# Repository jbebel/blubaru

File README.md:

# blubaru
Bluetooth interface for my 2000 Subaru Legacy

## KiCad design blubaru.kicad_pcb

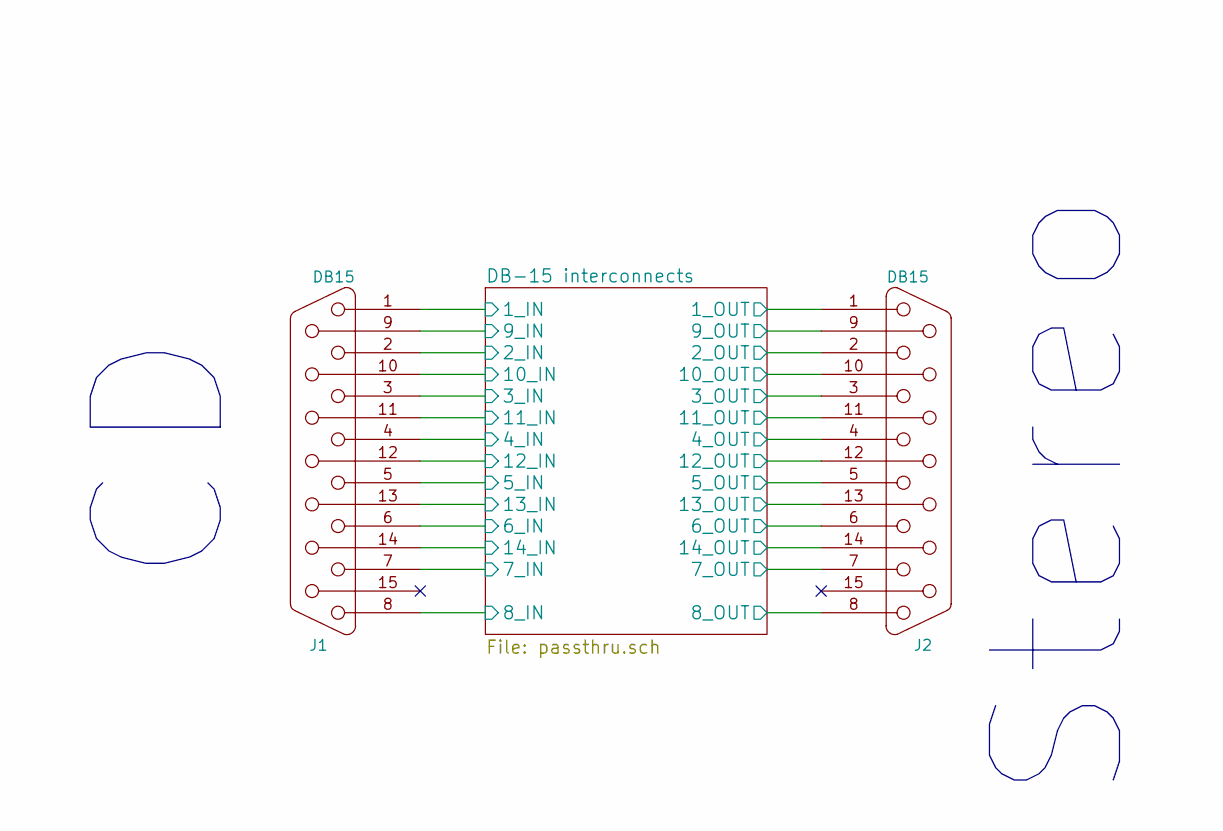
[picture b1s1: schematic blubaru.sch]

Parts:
J1: DB15; DB15FC
J2: DB15; DB15MC

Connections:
+BATT: J1.9, J2.9; also elsewhere on the board
/DB-15 interconnects/1_IN: J1.1, J2.1
/DB-15 interconnects/2_IN: J1.2; also elsewhere on the board
/DB-15 interconnects/2_OUT: J2.2; also elsewhere on the board
/DB-15 interconnects/3_IN: J1.3, J2.3
/DB-15 interconnects/4_IN: J1.4; also elsewhere on the board
/DB-15 interconnects/4_OUT: J2.4; also elsewhere on the board
/DB-15 interconnects/6_IN: J1.6; also elsewhere on the board
/DB-15 interconnects/6_OUT: J2.6; also elsewhere on the board
/DB-15 interconnects/7_IN: J1.7, J2.7
/DB-15 interconnects/8_IN: J1.8, J2.8
/DB-15 interconnects/10_IN: J1.10, J2.10
/DB-15 interconnects/11_IN: J1.11 (P111), J2.11 (P111)
/DB-15 interconnects/12_IN: J1.12, J2.12
/DB-15 interconnects/13_IN: J1.13, J2.13
GND: J1.14, J2.14; also elsewhere on the board
GNDA: J1.5, J2.5; also elsewhere on the board

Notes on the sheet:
Stereo

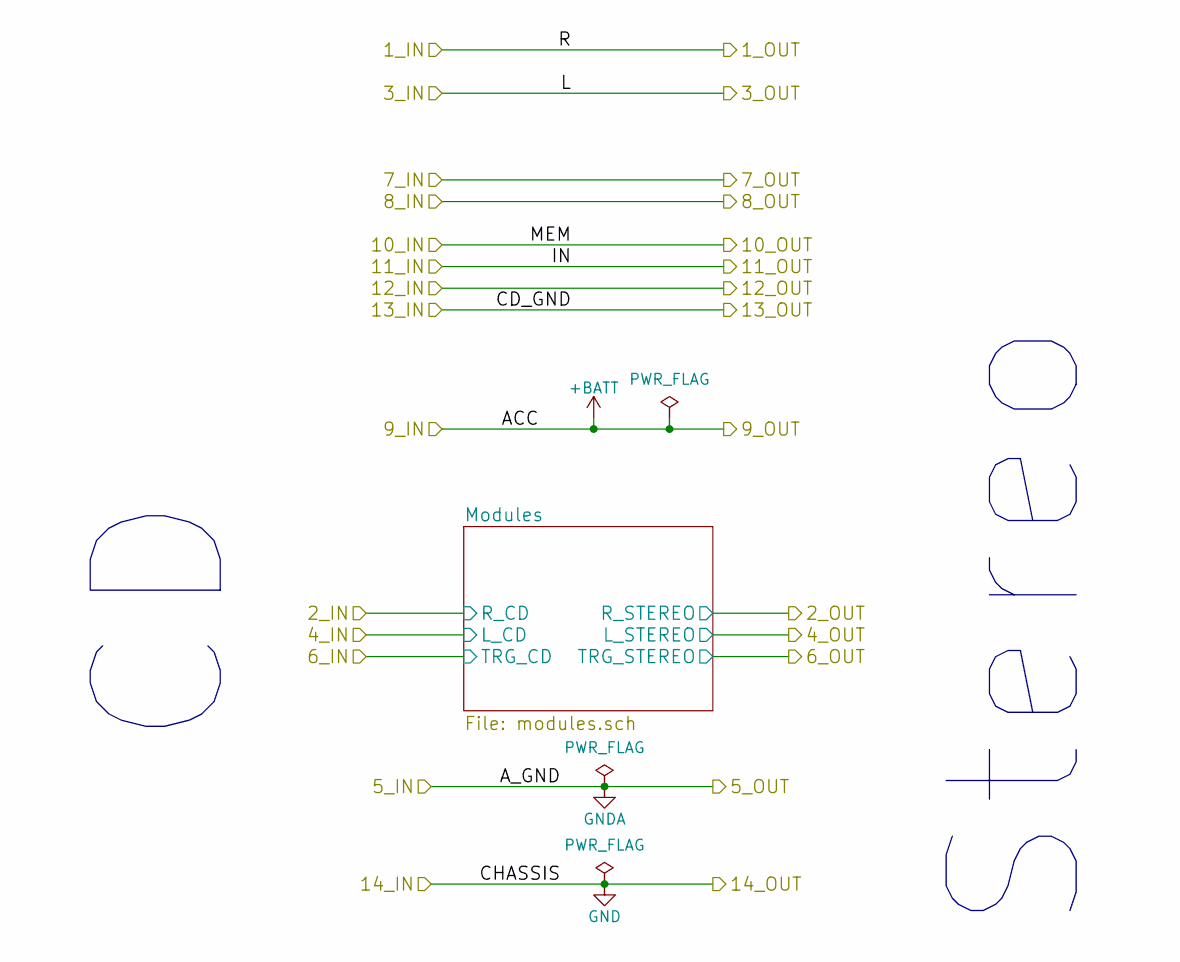
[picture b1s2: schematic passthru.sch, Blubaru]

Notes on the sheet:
Stereo

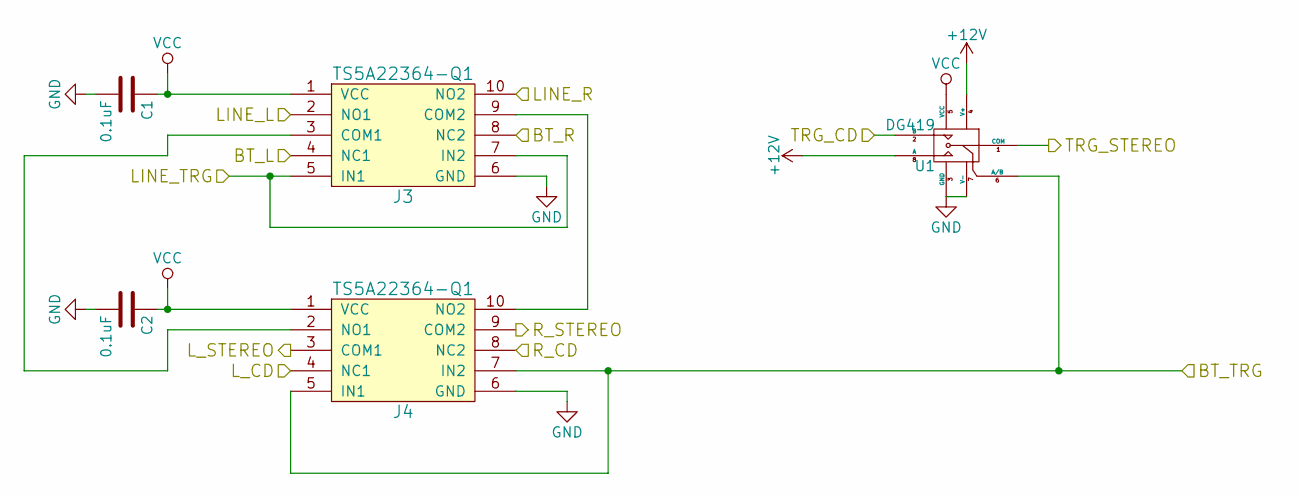
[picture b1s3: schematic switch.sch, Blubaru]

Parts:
C1, C2: 0.1uF; C_Disc_D4.0mm_W2.6mm_P2.50mm
J3, J4: TS5A22364-Q1
U1: DG419; DIP-8_W7.62mm

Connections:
+12V: U1.4 (V+), U1.8 (A); also elsewhere on the board
/DB-15 interconnects/2_IN: J4.8 (NC2); also elsewhere on the board
/DB-15 interconnects/2_OUT: J4.9 (COM2); also elsewhere on the board
/DB-15 interconnects/4_IN: J4.4 (NC1); also elsewhere on the board
/DB-15 interconnects/4_OUT: J4.3 (COM1); also elsewhere on the board
/DB-15 interconnects/6_IN: U1.2 (B); also elsewhere on the board
/DB-15 interconnects/6_OUT: U1.1 (COM); also elsewhere on the board
/DB-15 interconnects/Modules/Audio switch/BT_L: J3.4 (NC1); also elsewhere on the board
/DB-15 interconnects/Modules/Audio switch/BT_R: J3.8 (NC2); also elsewhere on the board
/DB-15 interconnects/Modules/Audio switch/BT_TRG: J4.5 (IN1), J4.7 (IN2), U1.6 (A/B); also elsewhere on the board
/DB-15 interconnects/Modules/Audio switch/LINE_L: J3.2 (NO1); also elsewhere on the board
/DB-15 interconnects/Modules/Audio switch/LINE_R: J3.10 (NO2); also elsewhere on the board
/DB-15 interconnects/Modules/Audio switch/LINE_TRG: J3.5 (IN1), J3.7 (IN2); also elsewhere on the board
GND: C1.2, C2.2, J3.6 (GND), J4.6 (GND), U1.3 (GND), U1.7 (V-); also elsewhere on the board
unnamed: J3.3 (COM1), J4.2 (NO1)
unnamed: J3.9 (COM2), J4.10 (NO2)
VCC: C1.1, C2.1, J3.1 (VCC), J4.1 (VCC), U1.5 (VCC); also elsewhere on the board

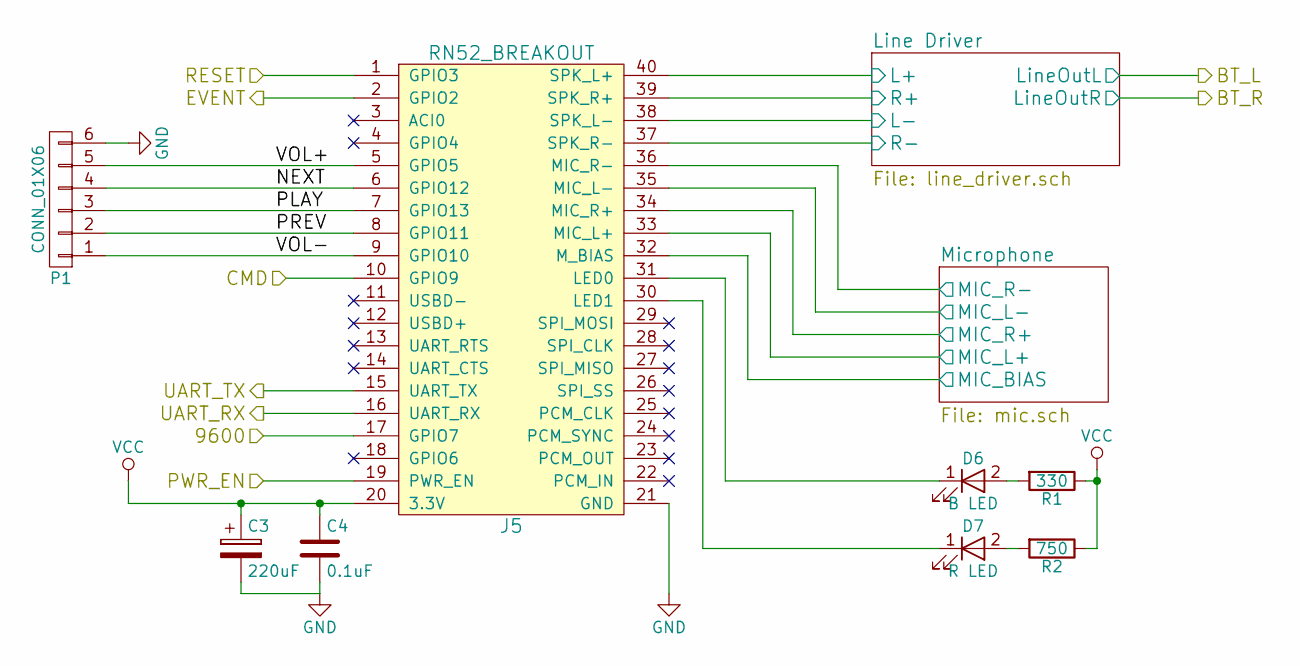
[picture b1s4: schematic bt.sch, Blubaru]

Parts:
C3: 220uF; CP_Radial_D6.3mm_P2.50mm
C4: 0.1uF; C_Disc_D4.0mm_W2.6mm_P2.50mm
D6: B LED; LED_D3.0mm_Horizontal_O1.27mm_Z6.0mm
D7: R LED; LED_D3.0mm_Horizontal_O1.27mm_Z6.0mm
J5: RN52_BREAKOUT; RN52_Breakout
P1: CONN_01X06; Pin_Header_Straight_1x06_Pitch2.54mm
R1: 330; R_Axial_DIN0204_L3.6mm_D1.6mm_P5.08mm_Horizontal
R2: 750; R_Axial_DIN0204_L3.6mm_D1.6mm_P5.08mm_Horizontal

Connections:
/DB-15 interconnects/Modules/Bluetooth Module/9600: J5.17 (GPIO7); also elsewhere on the board
/DB-15 interconnects/Modules/Bluetooth Module/CMD: J5.10 (GPIO9); also elsewhere on the board
/DB-15 interconnects/Modules/Bluetooth Module/EVENT: J5.2 (GPIO2); also elsewhere on the board
/DB-15 interconnects/Modules/Bluetooth Module/Line Driver/L+: J5.40 (SPK_L+); also elsewhere on the board
/DB-15 interconnects/Modules/Bluetooth Module/Line Driver/L-: J5.38 (SPK_L-); also elsewhere on the board
/DB-15 interconnects/Modules/Bluetooth Module/Line Driver/R+: J5.39 (SPK_R+); also elsewhere on the board
/DB-15 interconnects/Modules/Bluetooth Module/Line Driver/R-: J5.37 (SPK_R-); also elsewhere on the board
/DB-15 interconnects/Modules/Bluetooth Module/Microphone/MIC_BIAS: J5.32 (M_BIAS); also elsewhere on the board
/DB-15 interconnects/Modules/Bluetooth Module/Microphone/MIC_L+: J5.33 (MIC_L+); also elsewhere on the board
/DB-15 interconnects/Modules/Bluetooth Module/Microphone/MIC_L-: J5.35 (MIC_L-); also elsewhere on the board
/DB-15 interconnects/Modules/Bluetooth Module/Microphone/MIC_R+: J5.34 (MIC_R+); also elsewhere on the board
/DB-15 interconnects/Modules/Bluetooth Module/Microphone/MIC_R-: J5.36 (MIC_R-); also elsewhere on the board
/DB-15 interconnects/Modules/Bluetooth Module/NEXT: J5.6 (GPIO12), P1.4
/DB-15 interconnects/Modules/Bluetooth Module/PLAY: J5.7 (GPIO13), P1.3
/DB-15 interconnects/Modules/Bluetooth Module/PREV: J5.8 (GPIO11), P1.2
/DB-15 interconnects/Modules/Bluetooth Module/PWR_EN: J5.19 (PWR_EN); also elsewhere on the board
/DB-15 interconnects/Modules/Bluetooth Module/UART_RX: J5.16 (UART_RX); also elsewhere on the board
/DB-15 interconnects/Modules/Bluetooth Module/UART_TX: J5.15 (UART_TX); also elsewhere on the board
/DB-15 interconnects/Modules/Bluetooth Module/VOL+: J5.5 (GPIO5), P1.5
/DB-15 interconnects/Modules/Bluetooth Module/VOL-: J5.9 (GPIO10), P1.1
/DB-15 interconnects/Modules/Microcontroller/BT_RESET: J5.1 (GPIO3); also elsewhere on the board
GND: C3.2, C4.2, J5.21 (GND), P1.6; also elsewhere on the board
unnamed: D6.1 (K), J5.31 (LED0)
unnamed: D6.2 (A), R1.2
unnamed: D7.1 (K), J5.30 (LED1)
unnamed: D7.2 (A), R2.2
VCC: C3.1, C4.1, J5.20 (3.3V), R1.1, R2.1; also elsewhere on the board

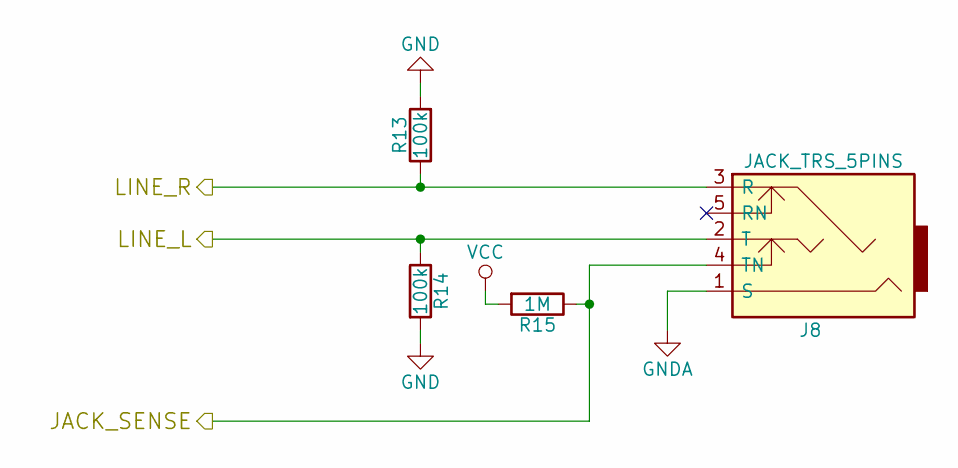
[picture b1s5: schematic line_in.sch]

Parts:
J8: JACK_TRS_5PINS; sj1-353xng
R13, R14: 100k; R_Axial_DIN0204_L3.6mm_D1.6mm_P5.08mm_Horizontal
R15: 1M; R_Axial_DIN0204_L3.6mm_D1.6mm_P5.08mm_Horizontal

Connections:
/DB-15 interconnects/Modules/Audio switch/LINE_L: J8.2 (T), R14.1; also elsewhere on the board
/DB-15 interconnects/Modules/Audio switch/LINE_R: J8.3 (R), R13.1; also elsewhere on the board
/DB-15 interconnects/Modules/Line In/JACK_SENSE: J8.4 (TN), R15.1; also elsewhere on the board
GND: R13.2, R14.2; also elsewhere on the board
GNDA: J8.1 (S); also elsewhere on the board
VCC: R15.2; also elsewhere on the board

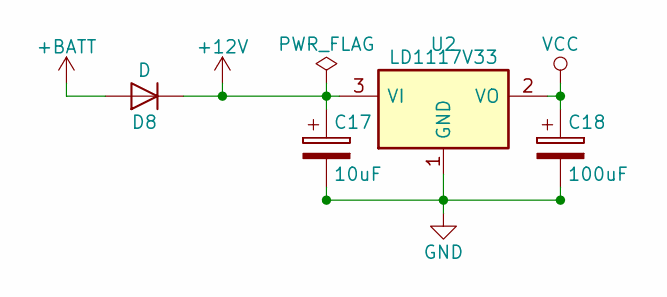
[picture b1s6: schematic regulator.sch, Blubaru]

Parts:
C17: 10uF; CP_Radial_D4.0mm_P1.50mm
C18: 100uF; CP_Radial_D6.3mm_P2.50mm
D8: D; D_DO-41_SOD81_P7.62mm_Horizontal
U2: LD1117V33; TO-220_Vertical

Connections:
+12V: C17.1, D8.1 (K), U2.3 (VI); also elsewhere on the board
+BATT: D8.2 (A); also elsewhere on the board
GND: C17.2, C18.2, U2.1 (GND); also elsewhere on the board
VCC: C18.1, U2.2 (VO); also elsewhere on the board

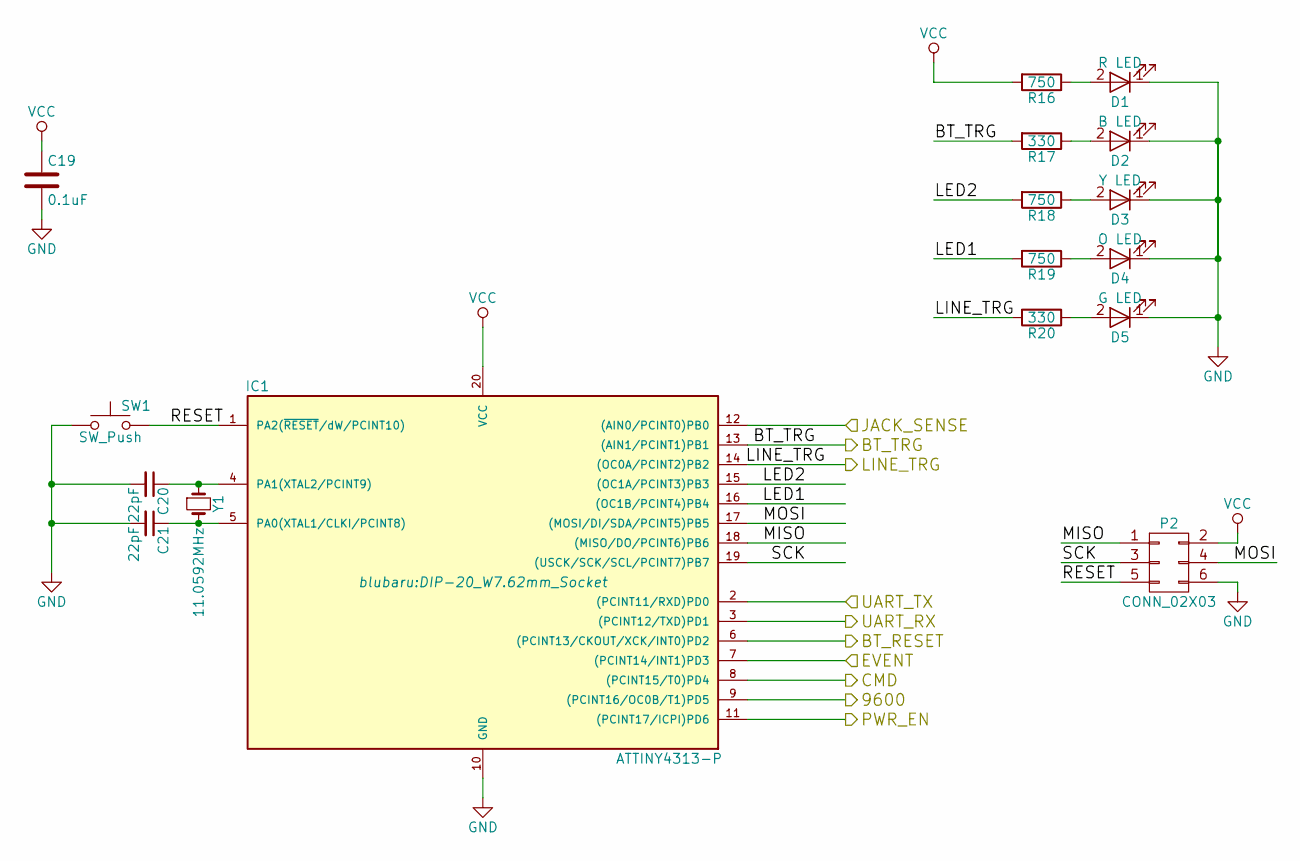
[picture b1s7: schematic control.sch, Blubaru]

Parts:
C19: 0.1uF; C_Disc_D4.0mm_W2.6mm_P2.50mm
C20, C21: 22pF; C_Disc_D4.0mm_W2.6mm_P2.50mm
D1: R LED; LED_D3.0mm_Horizontal_O1.27mm_Z6.0mm
D2: B LED; LED_D3.0mm_Horizontal_O1.27mm_Z6.0mm
D3: Y LED; LED_D3.0mm_Horizontal_O1.27mm_Z6.0mm
D4: O LED; LED_D3.0mm_Horizontal_O1.27mm_Z6.0mm
D5: G LED; LED_D3.0mm_Horizontal_O1.27mm_Z6.0mm
IC1: ATTINY4313-P; DIP-20_W7.62mm_Socket
P2: CONN_02X03; Pin_Header_Straight_2x03_Pitch2.54mm
R16, R18, R19: 750; R_Axial_DIN0204_L3.6mm_D1.6mm_P5.08mm_Horizontal
R17, R20: 330; R_Axial_DIN0204_L3.6mm_D1.6mm_P5.08mm_Horizontal
SW1: SW_Push; SW_Tactile_SPST_Angled_PTS645Vx58-2LFS
Y1: 11.0592MHz; Crystal_HC49-4H_Vertical

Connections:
/DB-15 interconnects/Modules/Audio switch/BT_TRG: IC1.13 ((AIN1/PCINT1)PB1), R17.2; also elsewhere on the board
/DB-15 interconnects/Modules/Audio switch/LINE_TRG: IC1.14 ((OC0A/PCINT2)PB2), R20.2; also elsewhere on the board
/DB-15 interconnects/Modules/Bluetooth Module/9600: IC1.9 ((PCINT16/OC0B/T1)PD5); also elsewhere on the board
/DB-15 interconnects/Modules/Bluetooth Module/CMD: IC1.8 ((PCINT15/T0)PD4); also elsewhere on the board
/DB-15 interconnects/Modules/Bluetooth Module/EVENT: IC1.7 ((PCINT14/INT1)PD3); also elsewhere on the board
/DB-15 interconnects/Modules/Bluetooth Module/PWR_EN: IC1.11 ((PCINT17/ICPI)PD6); also elsewhere on the board
/DB-15 interconnects/Modules/Bluetooth Module/UART_RX: IC1.3 ((PCINT12/TXD)PD1); also elsewhere on the board
/DB-15 interconnects/Modules/Bluetooth Module/UART_TX: IC1.2 ((PCINT11/RXD)PD0); also elsewhere on the board
/DB-15 interconnects/Modules/Line In/JACK_SENSE: IC1.12 ((AIN0/PCINT0)PB0); also elsewhere on the board
/DB-15 interconnects/Modules/Microcontroller/BT_RESET: IC1.6 ((PCINT13/CKOUT/XCK/INT0)PD2); also elsewhere on the board
/DB-15 interconnects/Modules/Microcontroller/LED1: IC1.16 ((OC1B/PCINT4)PB4), R19.2
/DB-15 interconnects/Modules/Microcontroller/LED2: IC1.15 ((OC1A/PCINT3)PB3), R18.2
/DB-15 interconnects/Modules/Microcontroller/MISO: IC1.18 ((MISO/DO/PCINT6)PB6), P2.1
/DB-15 interconnects/Modules/Microcontroller/MOSI: IC1.17 ((MOSI/DI/SDA/PCINT5)PB5), P2.4
/DB-15 interconnects/Modules/Microcontroller/RESET: IC1.1 (PA2(~RESET~/dW/PCINT10)), P2.5, SW1.2
/DB-15 interconnects/Modules/Microcontroller/SCK: IC1.19 ((USCK/SCK/SCL/PCINT7)PB7), P2.3
GND: C19.2, C20.2, C21.2, D1.1 (K), D2.1 (K), D3.1 (K), D4.1 (K), D5.1 (K), IC1.10 (GND), P2.6, SW1.1; also elsewhere on the board
unnamed: C20.1, IC1.4 (PA1(XTAL2/PCINT9)), Y1.1
unnamed: C21.1, IC1.5 (PA0(XTAL1/CLKI/PCINT8)), Y1.2
unnamed: D1.2 (A), R16.1
unnamed: D2.2 (A), R17.1
unnamed: D3.2 (A), R18.1
unnamed: D4.2 (A), R19.1
unnamed: D5.2 (A), R20.1
VCC: C19.1, IC1.20 (VCC), P2.2, R16.2; also elsewhere on the board

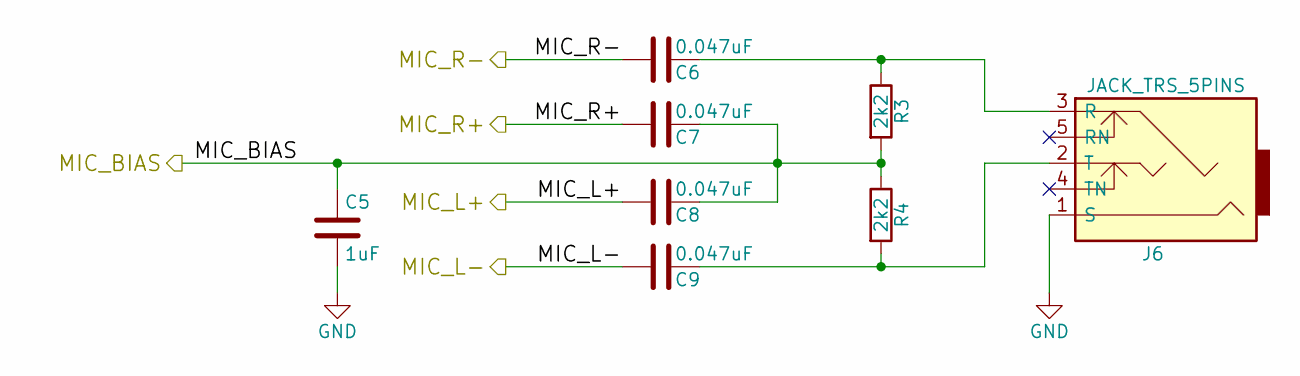
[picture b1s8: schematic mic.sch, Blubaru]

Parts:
C5: 1uF; C_Disc_D5.0mm_W3.2mm_P2.50mm
C6, C7, C8, C9: 0.047uF; C_Disc_D4.0mm_W2.6mm_P2.50mm
J6: JACK_TRS_5PINS; sj1-353xng
R3, R4: 2k2; R_Axial_DIN0204_L3.6mm_D1.6mm_P5.08mm_Horizontal

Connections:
/DB-15 interconnects/Modules/Bluetooth Module/Microphone/MIC_BIAS: C5.1, C7.1, C8.1, R3.2, R4.1; also elsewhere on the board
/DB-15 interconnects/Modules/Bluetooth Module/Microphone/MIC_L+: C8.2; also elsewhere on the board
/DB-15 interconnects/Modules/Bluetooth Module/Microphone/MIC_L-: C9.2; also elsewhere on the board
/DB-15 interconnects/Modules/Bluetooth Module/Microphone/MIC_R+: C7.2; also elsewhere on the board
/DB-15 interconnects/Modules/Bluetooth Module/Microphone/MIC_R-: C6.2; also elsewhere on the board
GND: C5.2, J6.1 (S); also elsewhere on the board
unnamed: C6.1, J6.3 (R), R3.1
unnamed: C9.1, J6.2 (T), R4.2

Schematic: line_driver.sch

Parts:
C10, C12, C14, C16: 1uF; CP_Radial_D4.0mm_P1.50mm
C11, C13, C15: 1uF; C_Disc_D5.0mm_W3.2mm_P2.50mm
J7: DRV632
R5, R8, R9, R12: 8.2k; R_Axial_DIN0204_L3.6mm_D1.6mm_P5.08mm_Horizontal
R6, R7, R10, R11: 11k; R_Axial_DIN0204_L3.6mm_D1.6mm_P5.08mm_Horizontal

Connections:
/DB-15 interconnects/Modules/Audio switch/BT_L: J7.3 (OUTR), R5.2; also elsewhere on the board
/DB-15 interconnects/Modules/Audio switch/BT_R: J7.12 (OUTL), R12.2; also elsewhere on the board
/DB-15 interconnects/Modules/Bluetooth Module/Line Driver/L+: C14.1; also elsewhere on the board
/DB-15 interconnects/Modules/Bluetooth Module/Line Driver/L-: C16.1; also elsewhere on the board
/DB-15 interconnects/Modules/Bluetooth Module/Line Driver/R+: C12.1; also elsewhere on the board
/DB-15 interconnects/Modules/Bluetooth Module/Line Driver/R-: C10.1; also elsewhere on the board
GND: C11.2, C15.2, J7.4 (GND), J7.10 (GND); also elsewhere on the board
GNDA: R8.1, R9.1; also elsewhere on the board
unnamed: C10.2, R6.1
unnamed: C11.1, J7.6 (VSS)
unnamed: C12.2, R7.1
unnamed: C13.1, J7.8 (CP)
unnamed: C13.2, J7.7 (CN)
unnamed: C14.2, R10.1
unnamed: C16.2, R11.1
unnamed: J7.1 (+INR), R7.2, R8.2
unnamed: J7.2 (-INR), R5.1, R6.2
unnamed: J7.13 (-INL), R11.2, R12.1
unnamed: J7.14 (+INL), R9.2, R10.2
VCC: C15.1, J7.5 (~MUTE), J7.9 (VDD); also elsewhere on the board

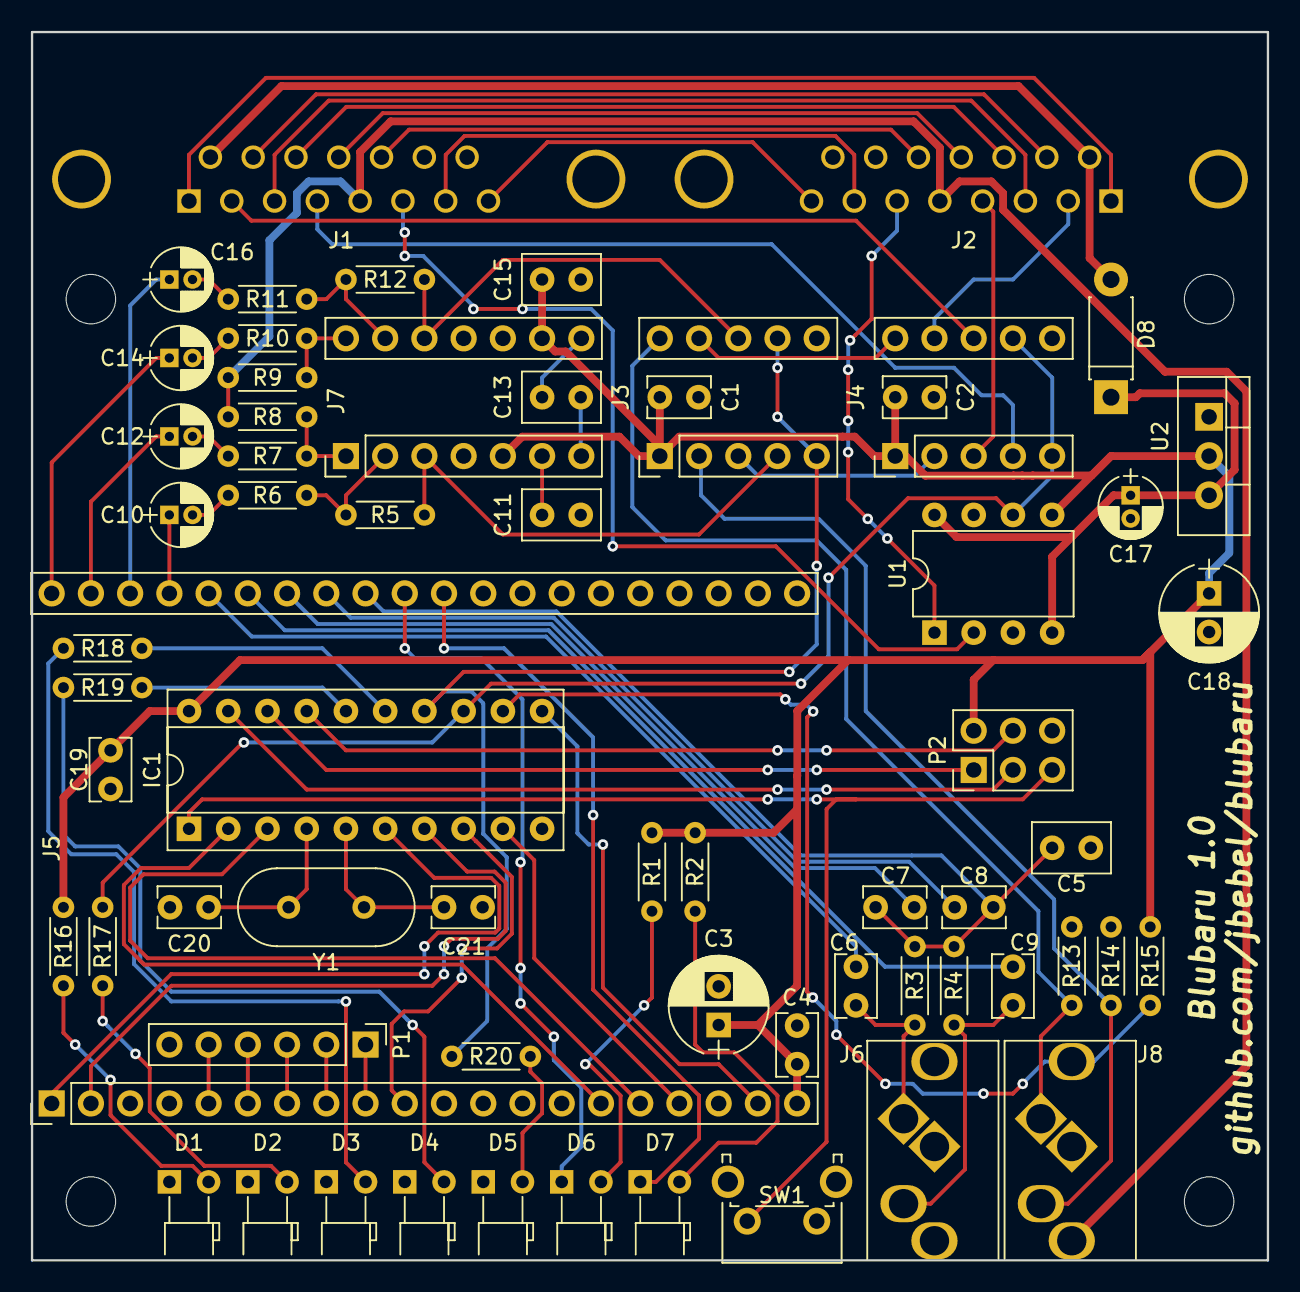
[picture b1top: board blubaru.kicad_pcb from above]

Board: 2 copper layers, 80.0 x 79.5 mm, 64 parts (0 on the bottom side), 79 nets.

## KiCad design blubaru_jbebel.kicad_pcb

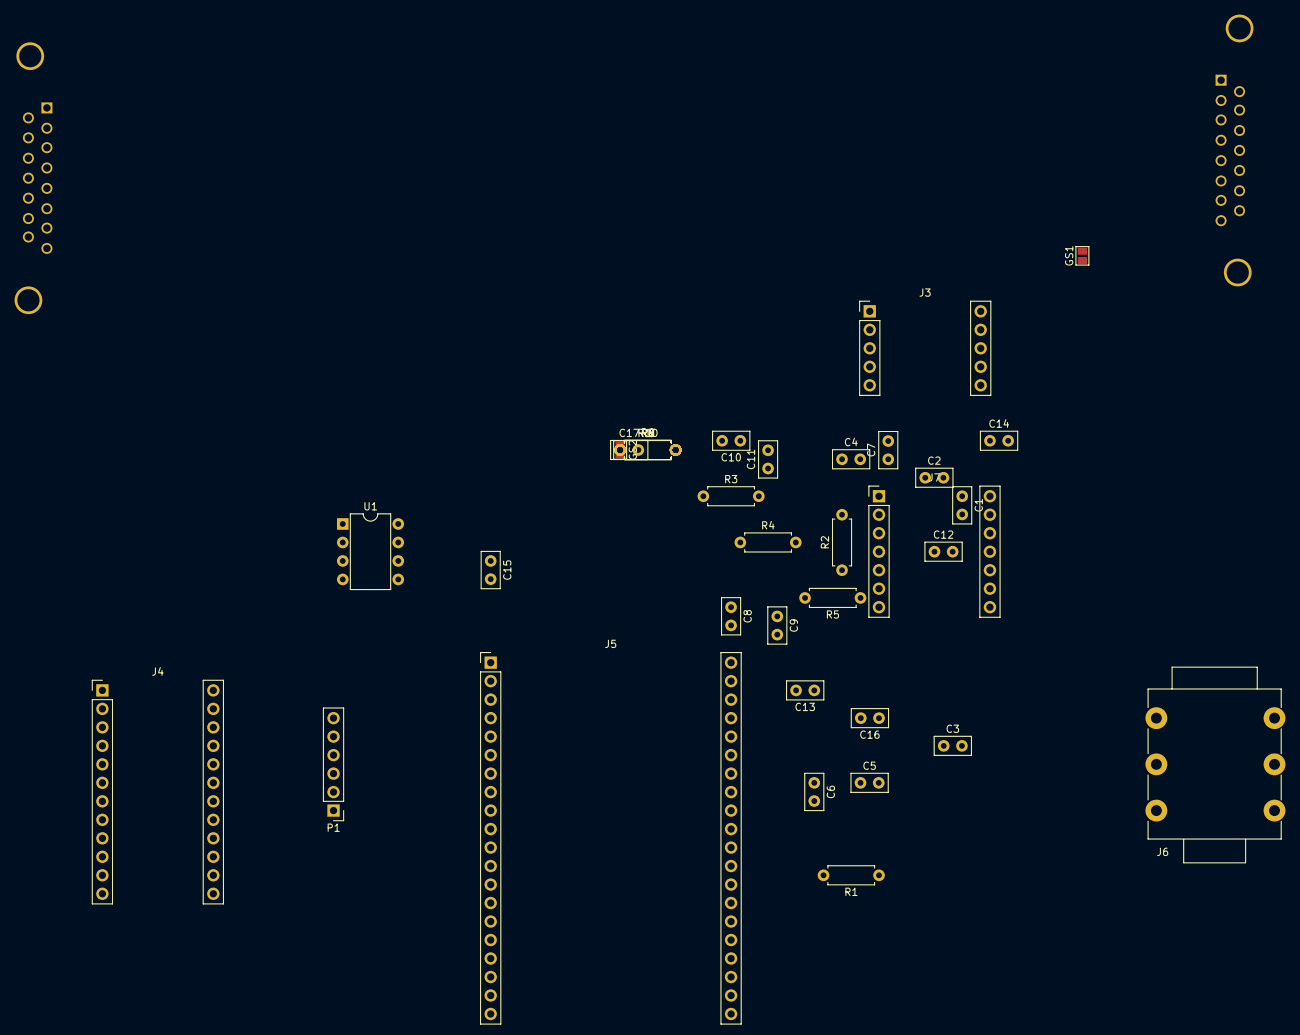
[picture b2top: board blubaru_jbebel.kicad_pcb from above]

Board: 2 copper layers, 38 parts (0 on the bottom side), 52 nets, no tracks yet.

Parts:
C1, C12: 0.1uF; C_Disc_D5.0mm_W2.5mm_P2.50mm
C2, C8, C9, C11, C13, C16: 1uF; C_Disc_D5.0mm_W2.5mm_P2.50mm
C3, C4, C5, C6: 47nF; C_Disc_D5.0mm_W2.5mm_P2.50mm
C7, C10, C14, C17: 100uF; C_Disc_D5.0mm_W2.5mm_P2.50mm
C15: 10uF; C_Disc_D5.0mm_W2.5mm_P2.50mm
GS1, GS2: GS2
J1: DB15; DB15FC
J2: DB15; DB15MC
J3: FSA2269
J4: ProMicro
J5: RN52_BREAKOUT; RN52_Breakout
J6: JACK_TRS_6PINS; NMJ6HCD2
J7: TPA6112
P1: CONN_01X06; Pin_Header_Straight_1x06_Pitch2.54mm
R1, R2: 2k2; R_Axial_DIN0207_L6.3mm_D2.5mm_P7.62mm_Horizontal
R3, R6, R7, R10: 47k; R_Axial_DIN0207_L6.3mm_D2.5mm_P7.62mm_Horizontal
R4, R5, R8, R9: 22k; R_Axial_DIN0207_L6.3mm_D2.5mm_P7.62mm_Horizontal
U1: DG419; DIP-8_W7.62mm

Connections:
+12V: J1.9, J2.9, J4.24, U1.4, U1.8
/DB-15 interconnects/1_IN: J1.1, J2.1
/DB-15 interconnects/2_IN: J1.2, J3.2
/DB-15 interconnects/2_OUT: J2.2, J3.5
/DB-15 interconnects/3_IN: J1.3, J2.3
/DB-15 interconnects/4_IN: J1.4, J3.10
/DB-15 interconnects/4_OUT: J2.4, J3.8
/DB-15 interconnects/5_IN: GS1.1, J1.5, J2.5
/DB-15 interconnects/6_IN: J1.6, U1.2
/DB-15 interconnects/6_OUT: J2.6, U1.1
/DB-15 interconnects/7_IN: J1.7, J2.7
/DB-15 interconnects/8_IN: J1.8, J2.8
/DB-15 interconnects/10_IN: J1.10, J2.10
/DB-15 interconnects/11_IN: J1.11, J2.11
/DB-15 interconnects/12_IN: J1.12, J2.12
/DB-15 interconnects/13_IN: GS2.1, J1.13, J2.13
/DB-15 interconnects/Modules/Audio switch/BT_L: C7.1, C10.1, J3.1
/DB-15 interconnects/Modules/Audio switch/BT_R: C14.1, C17.1, J3.3
/DB-15 interconnects/Modules/Audio switch/BT_TRG: J3.6, J3.7, J4.12, U1.6
/DB-15 interconnects/Modules/Bluetooth Module/Amp/L+: C8.2, J5.40
/DB-15 interconnects/Modules/Bluetooth Module/Amp/L-: C9.2, J5.38
/DB-15 interconnects/Modules/Bluetooth Module/Amp/R+: C13.2, J5.39
/DB-15 interconnects/Modules/Bluetooth Module/Amp/R-: C16.2, J5.37
/DB-15 interconnects/Modules/Bluetooth Module/CMD: J4.5, J5.10
/DB-15 interconnects/Modules/Bluetooth Module/EVENT: J4.6, J5.2
/DB-15 interconnects/Modules/Bluetooth Module/Microphone/MIC_BIAS: C2.1, C4.2, C6.2, J5.32, R1.2, R2.2
/DB-15 interconnects/Modules/Bluetooth Module/Microphone/MIC_L+: C4.1, J5.33
/DB-15 interconnects/Modules/Bluetooth Module/Microphone/MIC_L-: C5.2, J5.35
/DB-15 interconnects/Modules/Bluetooth Module/Microphone/MIC_R+: C6.1, J5.34
/DB-15 interconnects/Modules/Bluetooth Module/Microphone/MIC_R-: C3.2, J5.36
/DB-15 interconnects/Modules/Bluetooth Module/NEXT: J5.6, P1.4
/DB-15 interconnects/Modules/Bluetooth Module/PLAY: J5.7, P1.3
/DB-15 interconnects/Modules/Bluetooth Module/PREV: J5.8, P1.2
/DB-15 interconnects/Modules/Bluetooth Module/UART_RX: J4.1, J5.16
/DB-15 interconnects/Modules/Bluetooth Module/UART_TX: J4.2, J5.15
/DB-15 interconnects/Modules/Bluetooth Module/VOL+: J5.5, P1.5
/DB-15 interconnects/Modules/Bluetooth Module/VOL-: J5.9, P1.1
GND: C1.1, C2.2, C11.2, C12.1, C15.1, GS1.2, GS2.2, J1.14, J2.14, J3.4, J4.3, J4.4, J4.23, J5.21, J6.1, J7.1, J7.6, J7.7, J7.8, J7.9, J7.14, P1.6, U1.3, U1.7
unnamed: C3.1, J6.3, R2.1
unnamed: C5.1, J6.2, R1.1
unnamed: C8.1, R4.2
unnamed: C9.1, R5.2
unnamed: C7.2, C10.2, J7.2, R3.1
unnamed: C11.1, J7.5, R6.1, R7.2
unnamed: C13.1, R8.2
unnamed: C14.2, C17.2, J7.12, R10.1
unnamed: C16.1, R9.2
unnamed: J7.3, R3.2, R4.1
unnamed: J7.4, R5.1, R6.2
unnamed: J7.10, R7.1, R8.1
unnamed: J7.11, R9.1, R10.2
VCC: C1.2, C12.2, C15.2, J3.9, J4.21, J5.19, J5.20, J7.13, U1.5

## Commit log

2017-02-07 Initial commit with a few components.
2017-02-08 Make connections to components on amplifier.
2017-02-08 Add the RN52 to my library and schematic
2017-02-08 Add DB15s and a cap on the breakout.
2017-02-09 Add ProMicro board and DB15 labels
2017-02-10 Add a microphone jack
2017-02-11 Add a mic jack and a header for buttons.
2017-02-15 Make a virtual audio switch part.
2017-02-25 Break up into hierarchical sheets.
2017-02-28 Put parts in the audio switch page.
2017-03-03 Create footprints for breakout boards
2017-03-03 Actually save the schematics that I had open.
2017-03-03 Create pcb file with design rules matching oshpark
2017-03-04 Update footprints for passives.
2017-03-04 Added footprint for audio jack.
2017-03-07 Update footprints for breakouts and jack
2017-03-07 Make the pads oval so they don't touch.
2017-03-08 Add 3d model for audio jack
2017-03-08 Add a new 5-pin jack to schematic library and use it.
2017-03-08 re-pair new 5-pin jack with footprint
2017-03-08 Use a relative path to the 3d model
2017-03-08 Update netlist to use 5-pin jack
2017-03-09 Move everything up a directory
2017-03-10 Add datasheet links
2017-03-10 Switch pin headers to socket strips
2017-03-19 Correct footprints for caps and DB15s
2017-05-02 FIx labels
    Swapped incorrect L+ and L- labels
2017-05-05 Add an LED indicator to the trigger
2017-05-14 Add a line_driver schematic
    This branch contains the full line driver with 2nd order filter, which
    provides a low-pass filter on the input.
2017-05-14 Simple line driver
    Contains minimal components. no 2nd order low pass filter on input.
2017-05-15 Apparently something wasn't saved.
2017-05-31 Change the labelling for the MUTE input
2017-05-31 Adjust labelling on MUTE input
2017-06-01 Adjust label on DRV632 MUTE input
2017-06-01 Fix the schematic to use the new DRV632 component.
2017-06-02 Add keywords to part and datasheet to schematic for DRV632
2017-06-02 add component values and footprints.
2017-06-03 Add part for TS5A22364-Q1 and replace FSA2269 with it.
2017-06-03 Add a ProMini part, and genericize wiring to work with either.
2017-06-04 Add footprints for audio switch and amp.
2017-06-04 Add RC filter on line-outs, matching the EVM.
2017-06-05 Adjust some cap prefixes and add large CD/Stereo labels to top level pages.
2017-06-19 Add LEDs to MCU and polarized caps on line driver.
2017-06-19 Add resistor values to LEDs and a voltage regulator. Has power pin errors still.
2017-06-25 Voltage regulator adjustments and tidying
    Switch to LD1117 component and add decoupling caps.
    Add a decoupling cap to the audio switch
    Shift some status LEDs to modules layer
    Use ProMini instead of ProMicro
    Update BOM
    Update netlist
2017-06-28 Add new capacitor footprints and associate them.
2017-06-28 Apply new footprints to net file and BOM.
2017-06-28 Add some datasheets to footprints
2017-06-28 Add some datasheets to schematics.
2017-06-28 Regenerate BOM and net with new datasheets.
2017-06-28 Fix 3D model scale for some caps.
2017-07-06 Fix labels and lay resistors flat.
    Left inputs to the line driver were backwards, because the datasheet had
    an error. I think I "fixed"it before to match the datasheet.
    I also decided to lay the resistors flat. They don't take up that much
    room flat, and they will be easier to make pretty on the board, and more
    stable with all the vibration.
    Also updated the BOM and netlist.
2017-07-28 Add a line in module and use a smaller jack.
    Lots of changes:
    Added a line in. This requires another audio switch, so that's added to
    the audio switch module.
    Also, since I'm using two jacks, I chose a smaller jack module. This
    needed a new footprint, and a new 3d model. The footprint is trickier,
    since it really needed slots, which OSH won't guarantee. I've given it a
2017-09-13 fix the driver labels
2017-09-13 Fix line driver labels
2017-09-13 Reduce the line driver back to simple
    After determining the gain needed to be 0.735 (which is out of spec for
    the amp), I was unsure what to do with the 2nd order filter on the amp.
    It wasn't even present on the headphone amp from before, and I suspect
    the head unit in the car does some filtering of its own. To simplify
    things, I removed the second order filter and went back to a simple line
    driver. I also set the values of the gain setting resistors to 8.2 and
2017-09-19 Separate audio ground from power ground
    The connection between the CD player and stereo has a separate line for
    audio ground and the chassis ground. I didn't previously understand why
    this was necessary, so I tied them together. They were tied together in
    the stereo anyway. The reason is that when using power, there must be
    current returning on the ground line, and since that ground line is not
    free of resistance, that causes a slight voltage change. That voltage
2017-09-26 Adjust some positioning for better readability
2017-09-26 Fix page layout for two that were still on A4.
2017-11-03 Major update to use Atmel ATTINY4313
    Replace Pro Micro as microcontroller. Mostly contianed within the
    control sheet.
    Moved LEDs all onto control sheet.
    Updated a few capacitors.
    Added a reset switch. Still need to decide part.
    Updated a few capacitor models for 4.0.7
2017-11-23 Add LEDs to BT module
    These already exist on the breakout board, but they will be more visible
    if I add resistors to the front panel. They can be removed if space is
    limited and the case is translucent, but add them for now. In V2, there
    won't be a breakout board, so adding them now makes the V1 to V2 fewer
    changes.
2017-12-17 Add footprints for LEDs and tactile switches
    Also create an initial layout for fun.
2017-12-17 Add a better footprint for the regulator
2017-12-18 Clean up some schematics for readability.
    Run 12V from after power protection diode.
2017-12-18 Rough layout with short audio path.
2017-12-18 Add an outline for the BT antenna.
2017-12-18 fix path to audio jack 3d model.
2017-12-18 Update layout with new netlist
2017-12-18 First feasible layout.
2017-12-18 Re-add MCU footprint and use vertical regul.
2017-12-18 Remove extraneous center line from LEDs
2017-12-18 Power and audio paths connected.
2017-12-18 Fixup mic jack parts after schematic change (rebase).
    Some parts got flipped in 04f718b, onto which subsequent comments got rebased
    later.
2018-01-11 Rename the bluetooth reset line
    This is needed so it doesn't conflict with the MCU reset line of the
    same name. Apparently that puts them on the same net.
    Also, reorder the LEDs so they have nicer numbers on the board.
2018-01-11 Update net names, re-arrange LEDs
    Separated the RESET and BT_RESET nets. They collided previously.
    Renamed components after a few things shifted around.
    Moved LEDs around so they are in order.
2018-01-20 Fix lack of junction to GNDA, and route traces.
2018-02-08 jbebels attempt at routing
    All power and audio is routed, as is the crystal and UART lines. Other
    digital lines remain, and the resistors for the LEDs are moved off-board
    until I figure out the best place for them.
    This also required a small fix to the schematic. A junction was missing,
    causing the audio grounds to not be connected to the cd/stereo audio
    ground.
2018-02-22 First full layout
    I renumbered pins on the MCU so that the layout was cleaner, hence the
    regenerated net file.
    This passes all the design rules and nothing is unconnected. I managed
    to get the ground pour connected without having to pour between pins,
    but it seems even better connected if I do, and it is within the design
    rules, so it seems safe.
2018-03-15 Adjust some tolerances around traces and vias.
2018-03-16 More layout tweaks for tolerances and appearance.
2018-03-16 Add some logos to the back.
2018-03-16 Remove obsolete _rpwoodbu layout.
2018-05-31 Include more layers in layout view
    Also include PDF of schematic and layout, as well as a png of the 3D
    view.
